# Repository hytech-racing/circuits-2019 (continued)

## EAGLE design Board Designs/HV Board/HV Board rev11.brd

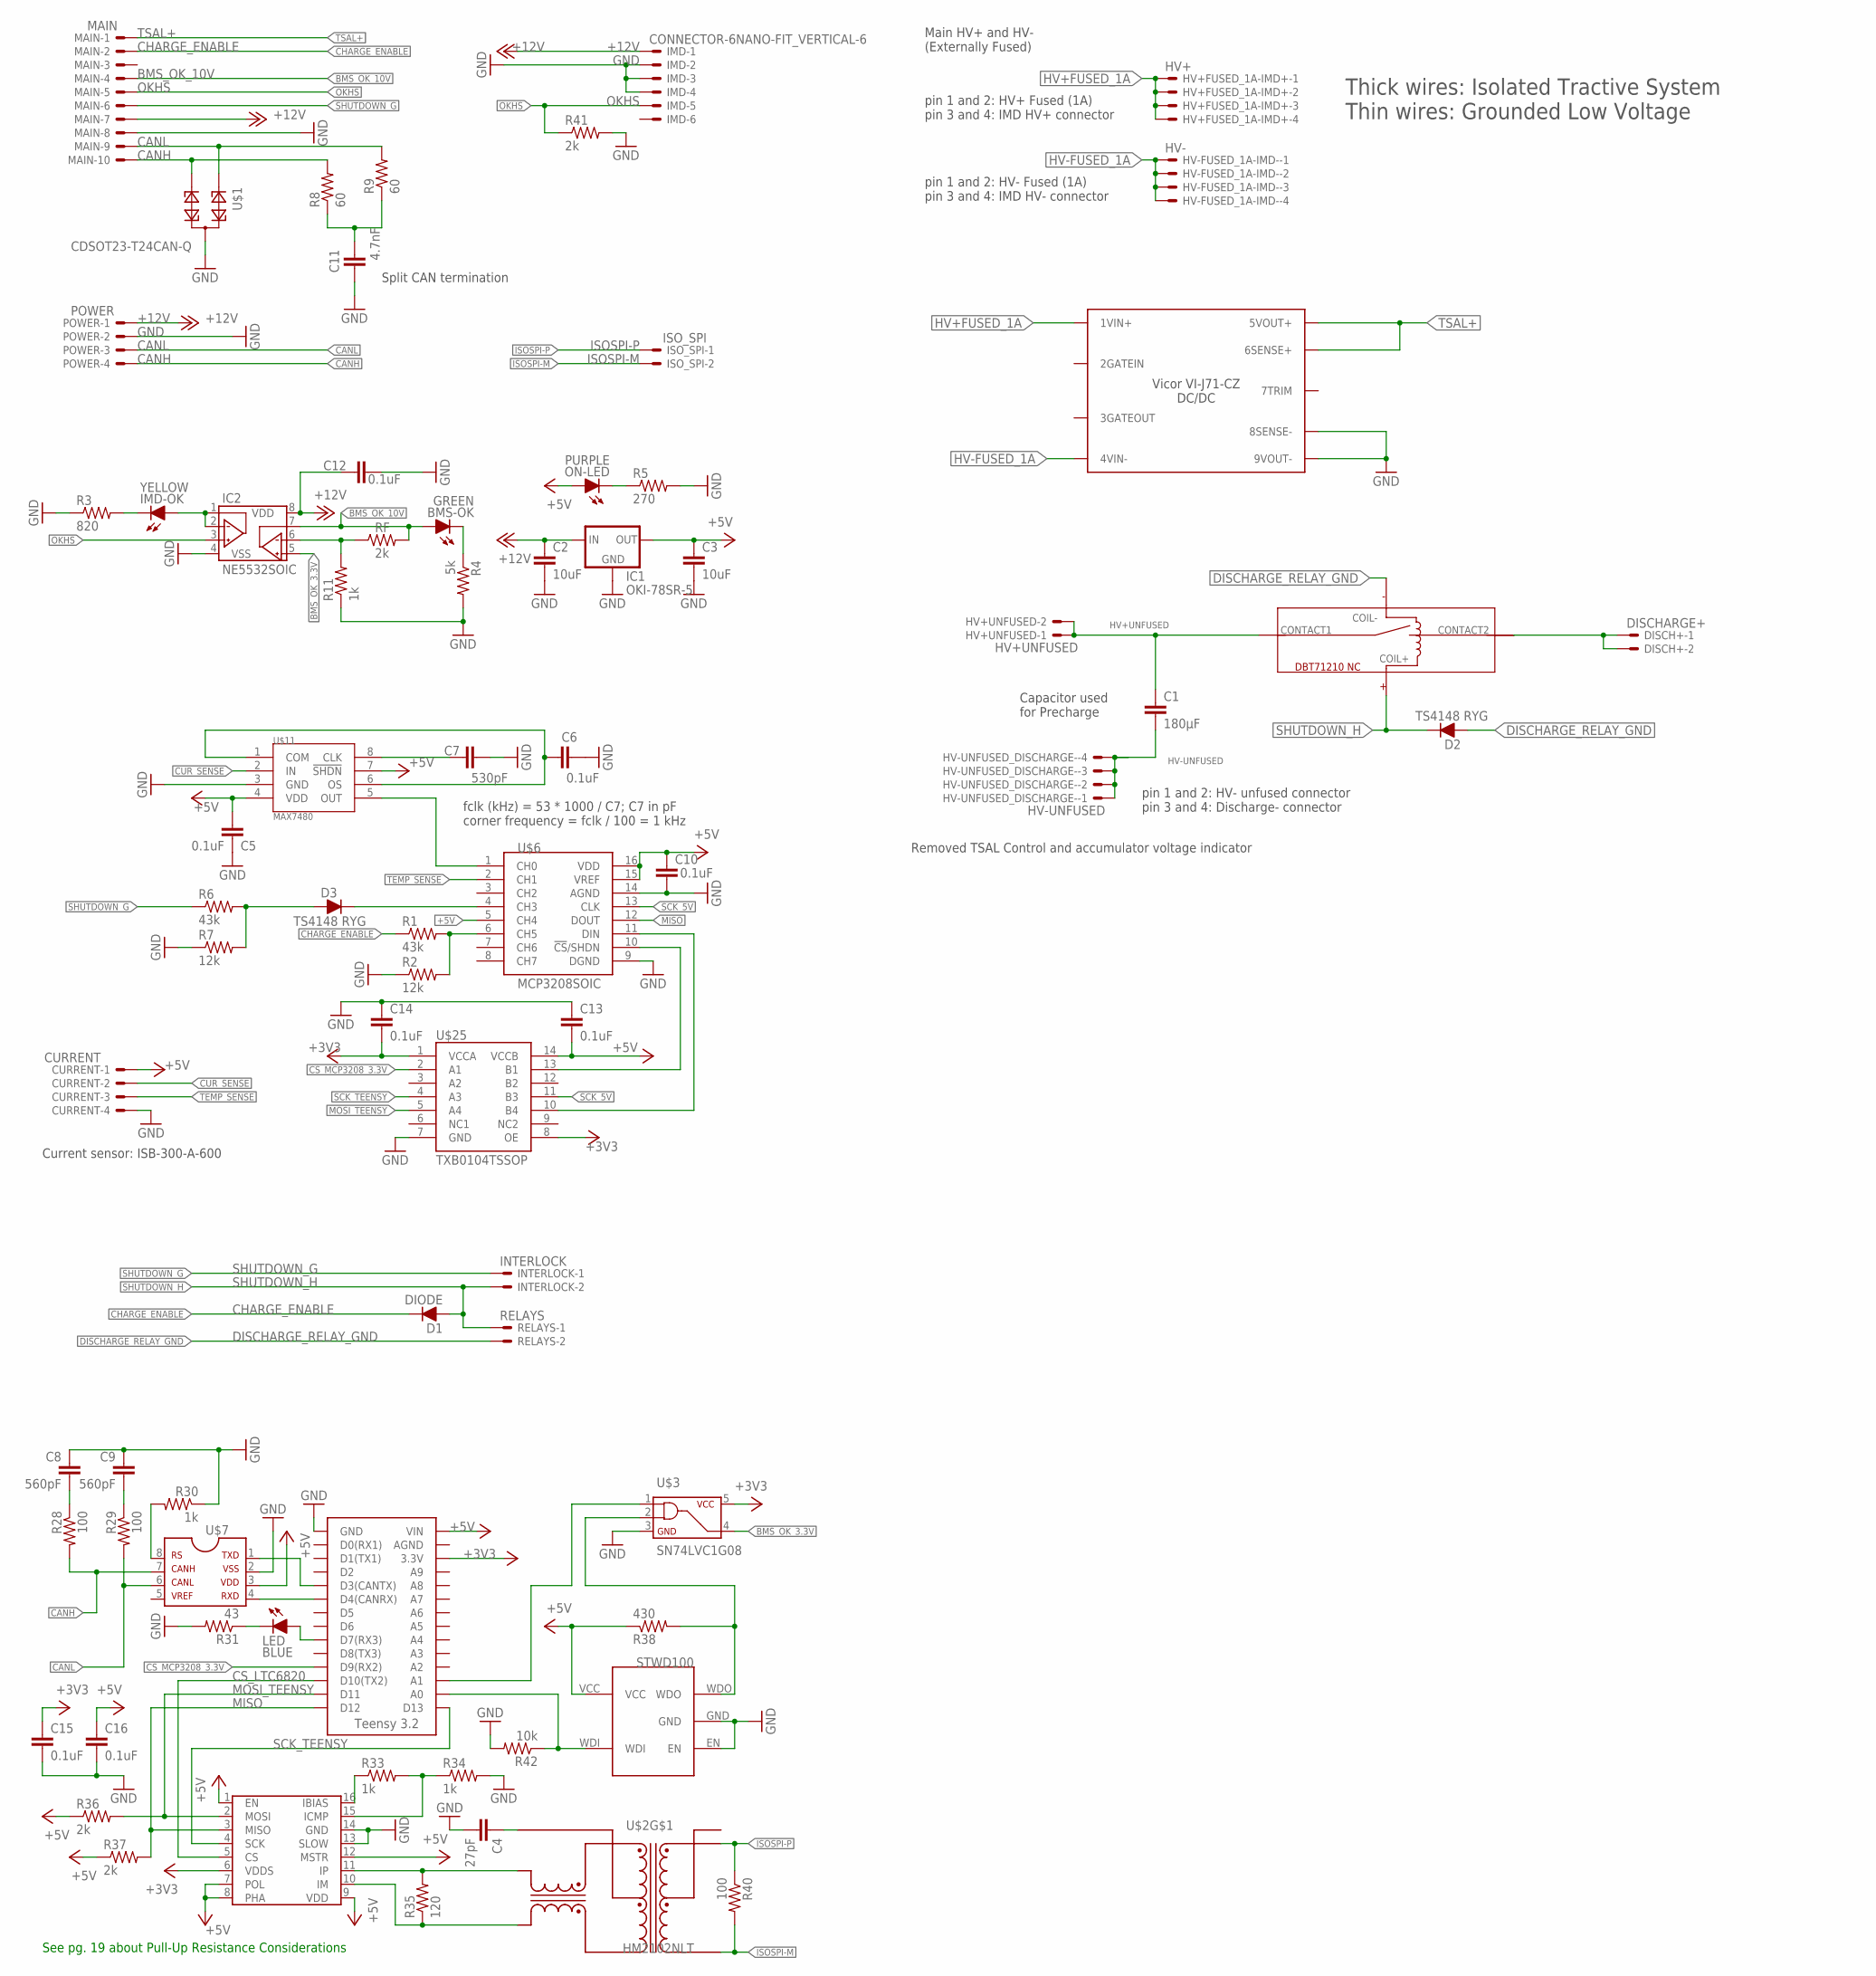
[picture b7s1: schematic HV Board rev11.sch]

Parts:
BMS-OK: GREEN; LED-805
C1: 180µF; LLS2V221MELZ
C2, C3: 10uF; 0805
C4: 27pF; 0805
C5, C6, C10, C12, C13, C14, C15, C16: 0.1uF; 0805
C7: 530pF; 0805
C8, C9: 560pF; 0805
C11: 4.7nF; 0805
CURRENT: CURRENT; NANO-FIT_VERTICAL-4
D1: DIODE; DO-41
D2, D3: TS4148 RYG; 0805_D
DISCH+: DISCHARGE+; NANO-FIT_VERTICAL-2
HV+FUSED_1A-IMD+: HV+; NANO-FIT_VERTICAL-4
HV+UNFUSED: HV+UNFUSED; NANO-FIT_VERTICAL-2
HV-FUSED_1A-IMD-: HV-; NANO-FIT_VERTICAL-4
HV-UNFUSED_DISCHARGE-: HV-UNFUSED; NANO-FIT_VERTICAL-4
IC1: OKI-78SR-5; OKI-78SR
IC2: NE5532SOIC; SOIC-08
IMD: CONNECTOR-6NANO-FIT_VERTICAL-6; NANO-FIT_VERTICAL-6
IMD-OK: YELLOW; LED-805
INTERLOCK: INTERLOCK; NANO-FIT_VERTICAL-2
ISO_SPI: ISO_SPI; NANO-FIT_VERTICAL-2
LED: BLUE; LED-805
MAIN: MAIN; NANO-FIT_VERTICAL-10
ON-LED: PURPLE; LED-805
POWER: POWER; NANO-FIT_VERTICAL-4
R1, R6: 43k; 0805
R2, R7: 12k; 0805
R3: 820; 0805
R4: 5k; 0805
R5: 270; 0805
R8, R9: 60; 0805
R11, R30, R33, R34: 1k; 0805
R28, R29, R40: 100; 0805
R31: 43; 0805
R35: 120; 0805
R36, R37, R41: 2k; 0805
R38: 430; 0805
R42: 10k; 0805
RELAYS: RELAYS; NANO-FIT_VERTICAL-2
RF: 2k; 0805
U$1: CDSOT23-T24CAN-Q; SOT23
U$2: HM2102NLT
U$3: SN74LVC1G08; SOT-23-5
U$4: DBT71210
U$5: HV_DCDC_VI-J71-CZ
U$6: MCP3208SOIC; SOIC-16
U$7: MCP2551; SOIC-08
U$8: LTC6820; MSOP-16
U$9: TEENSY_3.2_SIMPLE
U$10: STWD100; SOT23-5
U$11: MAX7480; SOIC-08
U$25: TXB0104TSSOP; TSSOP-14

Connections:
+3V3: C14.1, C15.2, U$3.5, U$8.6 (VDDS), U$9.3.3V, U$25.1 (VCCA), U$25.8 (OE)
+5V: C3.1, C5.1, C10.1, C13.1, C16.2, CURRENT.P$1, IC1.3 (OUT), ON-LED.A, R36.1, R37.1, R38.1, U$6.5 (CH4), U$6.15 (VREF), U$6.16 (VDD), U$7.3, U$8.1 (EN), U$8.7 (POL), U$8.8 (PHA), U$8.9 (VDD), U$8.12 (MSTR), U$9.VIN, U$10.VCC, U$11.4 (VDD), U$25.14 (VCCB)
+12V: C2.1, C12.1, IC1.1 (IN), IC2.8 (VDD), IMD.P$1, MAIN.P$7, POWER.P$1
BMS_OK_3.3V: IC2.5 (VINB+), U$3.4
BMS_OK_10V: BMS-OK.A, IC2.7 (VOUTB), MAIN.P$4, RF.2
CANH: MAIN.P$10, POWER.P$4, R8.2, R28.2, U$1.2, U$7.7
CANL: MAIN.P$9, POWER.P$3, R9.2, R29.2, U$1.1, U$7.6
CHARGE_ENABLE: D1.C, MAIN.P$2, R1.1
CS_LTC6820: U$8.5 (CS), U$9.D10(TX2)
CS_MCP3208_3.3V: U$9.D9(RX2), U$25.2 (A1)
CUR_SENSE: CURRENT.P$2, U$11.2 (IN)
DISCHARGE_RELAY_GND: D2.A, RELAYS.P$2, U$4.COIL-
GND: C2.2, C3.2, C4.2, C5.2, C6.2, C7.2, C8.1, C9.1, C10.2, C11.1, C12.2, C13.2, C14.2, C15.1, C16.1, CURRENT.P$4, IC1.2 (GND), IC2.4 (VSS), IMD.P$2, IMD.P$3, IMD.P$4, MAIN.P$8, POWER.P$2, R2.1, R3.1, R4.2, R5.2, R7.1, R11.1, R30.1, R31.2, R34.2, R41.2, R42.2, U$1.3, U$3.3, U$5.8SENSE-, U$5.9VOUT-, U$6.9 (DGND), U$6.14 (AGND), U$7.2, U$8.13 (SLOW), U$8.14 (GND), U$9.GND, U$10.EN, U$10.GND, U$11.3 (GND), U$25.7 (GND)
HV+FUSED_1A: HV+FUSED_1A-IMD+.P$1, HV+FUSED_1A-IMD+.P$2, HV+FUSED_1A-IMD+.P$3, HV+FUSED_1A-IMD+.P$4, U$5.1VIN+
HV+UNFUSED: C1.P$1 (1), HV+UNFUSED.P$1, HV+UNFUSED.P$2, U$4.CONTACT1
HV+UNFUSED_FSAE_DISCHARGE: DISCH+.P$1, DISCH+.P$2, U$4.CONTACT2
HV-FUSED_1A: HV-FUSED_1A-IMD-.P$1, HV-FUSED_1A-IMD-.P$2, HV-FUSED_1A-IMD-.P$3, HV-FUSED_1A-IMD-.P$4, U$5.4VIN-
HV-UNFUSED: C1.P$2 (2), HV-UNFUSED_DISCHARGE-.P$1, HV-UNFUSED_DISCHARGE-.P$2, HV-UNFUSED_DISCHARGE-.P$3, HV-UNFUSED_DISCHARGE-.P$4
IM: R35.1, U$2.P$10 (TD-), U$8.10 (IM)
IP: R35.2, U$2.P$12 (TD+), U$8.11 (IP)
ISOSPI-M: ISO_SPI.P$2, R40.2, U$2.P$3 (MX-)
ISOSPI-P: ISO_SPI.P$1, R40.1, U$2.P$1 (MX+)
MISO: R37.2, U$6.12 (DOUT), U$8.3 (MISO), U$9.D12
MOSI_5V: U$6.11 (DIN), U$25.10 (B4)
MOSI_TEENSY: R36.2, U$8.2 (MOSI), U$9.D11, U$25.5 (A4)
unnamed: U$6.1 (CH0), U$11.5 (OUT)
unnamed: C6.1, U$11.1 (COM), U$11.6 (OS)
unnamed: ON-LED.C, R5.1
unnamed: C7.1, U$11.8 (CLK)
unnamed: U$6.10 (!CS!/SHDN), U$25.13 (B1)
unnamed: D3.A, R6.2, R7.2
unnamed: D3.C, U$6.4 (CH3)
unnamed: C11.2, R8.1, R9.1
unnamed: IC2.6 (VINB-), R11.2, RF.1
unnamed: R1.2, R2.2, U$6.6 (CH5)
unnamed: U$7.1, U$9.D3(CANTX)
unnamed: R30.2, U$7.8
unnamed: C8.2, R28.1
unnamed: C9.2, R29.1
unnamed: LED.C, R31.1
unnamed: R33.1, U$8.16 (IBIAS)
unnamed: R33.2, R34.1, U$8.15 (ICMP)
unnamed: C4.1, U$2.P$11 (TCT)
unnamed: U$7.4, U$9.D4(CANRX)
unnamed: LED.A, U$9.D7(RX3)
unnamed: R38.2, U$3.2, U$10.WDO
unnamed: U$3.1, U$9.A1
unnamed: IC2.1 (VOUTA), IC2.2 (VINA-), IMD-OK.A
unnamed: BMS-OK.C, R4.1
unnamed: IMD-OK.C, R3.2
unnamed: R42.1, U$9.A0, U$10.WDI
OKHS: IC2.3 (VINA+), IMD.P$5, MAIN.P$5, R41.1
SCK_5V: U$6.13 (CLK), U$25.11 (B3)
SCK_TEENSY: U$8.4 (SCK), U$9.D13, U$25.4 (A3)
SHUTDOWN_G: INTERLOCK.P$1, MAIN.P$6, R6.1
SHUTDOWN_H: D1.A, D2.C, INTERLOCK.P$2, RELAYS.P$1, U$4.COIL+
TEMP_SENSE: CURRENT.P$3, U$6.2 (CH1)
TSAL+: MAIN.P$1, U$5.5VOUT+, U$5.6SENSE+

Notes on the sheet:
Current sensor: ISB-300-A-600
Main HV+ and HV- (Externally Fused)
Thick wires: Isolated Tractive System Thin wires: Grounded Low Voltage
See pg. 19 about Pull-Up Resistance Considerations
Capacitor used for Precharge
Removed TSAL Control and accumulator voltage indicator
pin 1 and 2: HV+ Fused (1A) pin 3 and 4: IMD HV+ connector
pin 1 and 2: HV- Fused (1A) pin 3 and 4: IMD HV- connector
pin 1 and 2: HV- unfused connector pin 3 and 4: Discharge- connector
fclk (kHz) = 53 * 1000 / C7; C7 in pF corner frequency = fclk / 100 = 1 kHz
Split CAN termination

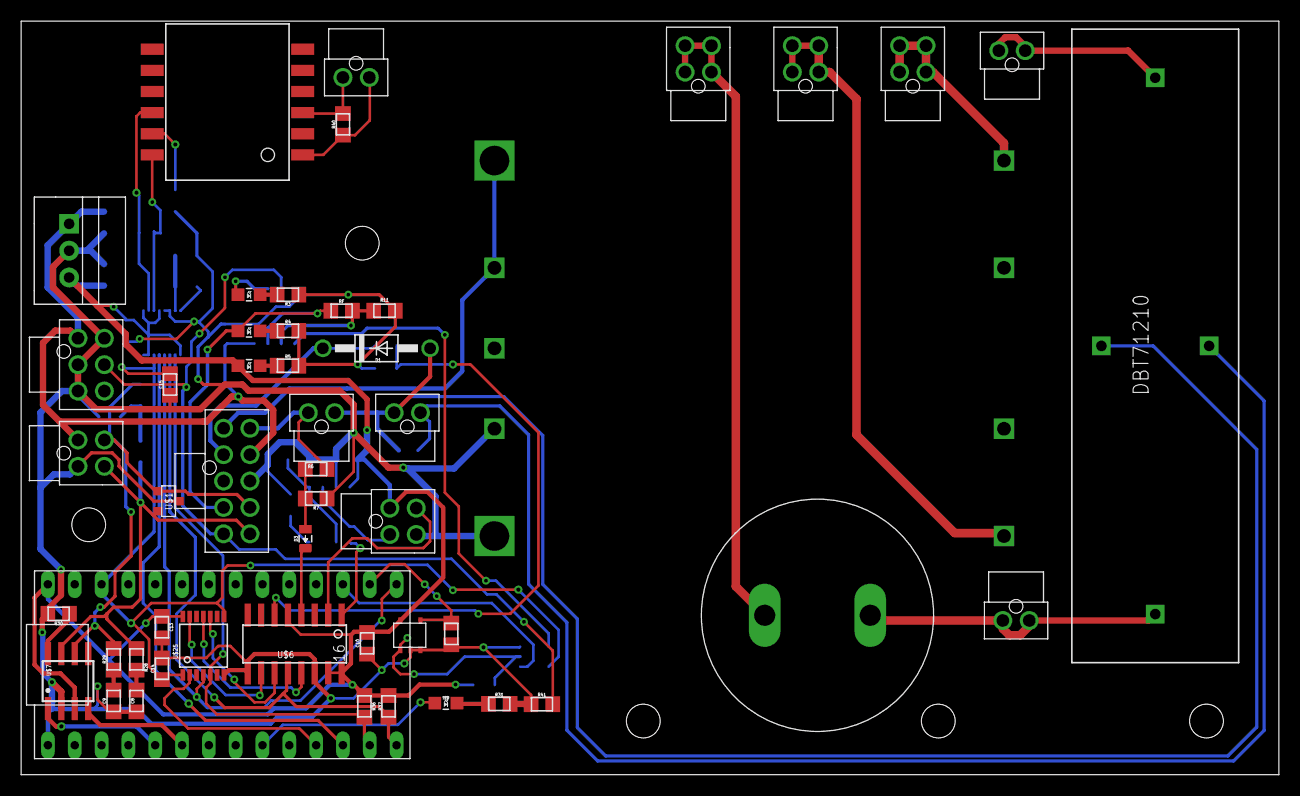
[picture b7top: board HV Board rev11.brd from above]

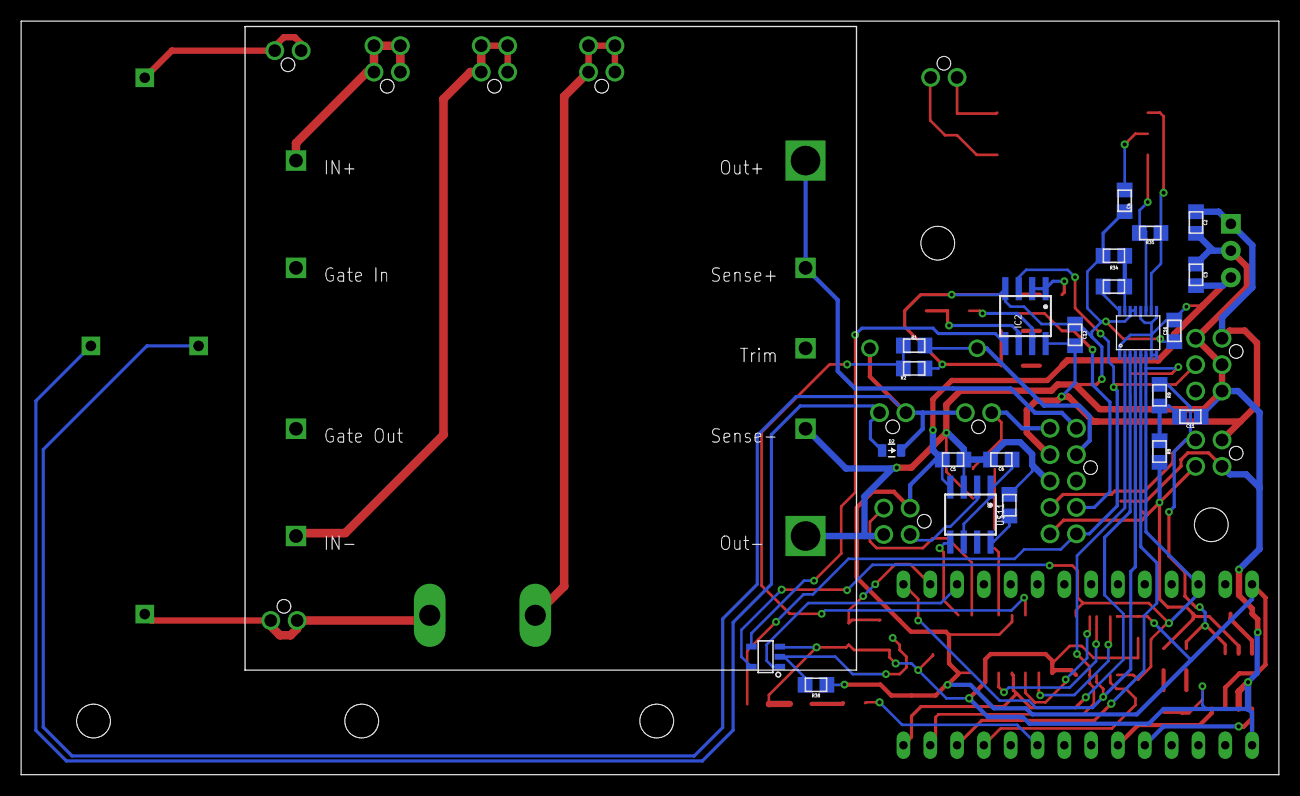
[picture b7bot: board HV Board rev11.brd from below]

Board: 2 copper layers, 119.1 x 71.4 mm, 73 parts (23 on the bottom side), 58 nets.

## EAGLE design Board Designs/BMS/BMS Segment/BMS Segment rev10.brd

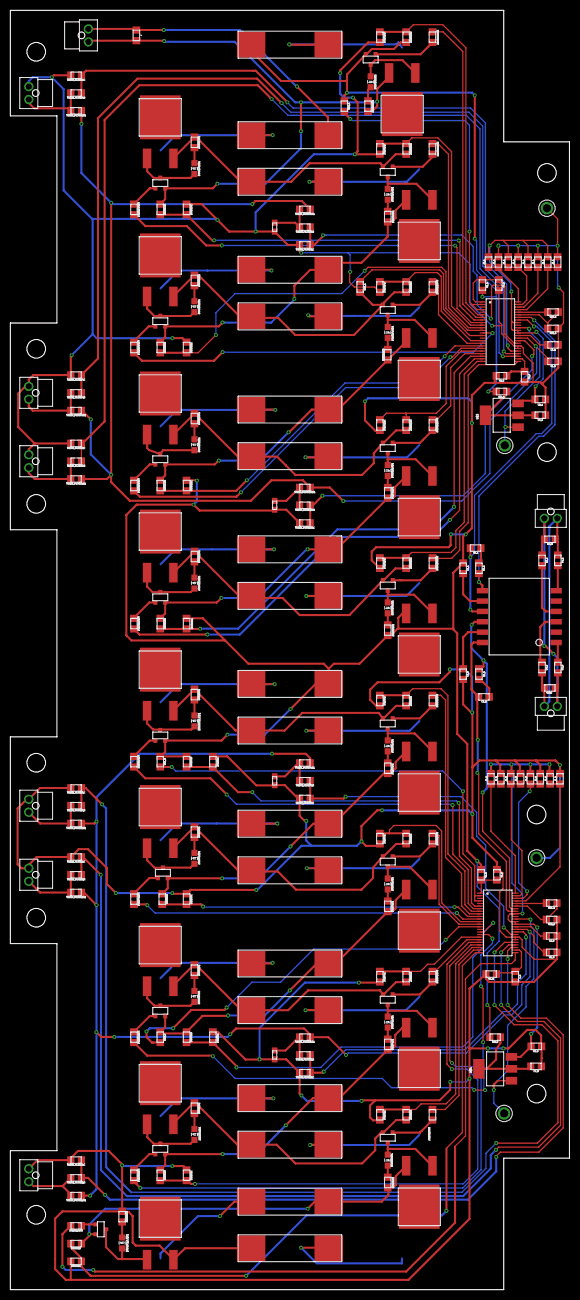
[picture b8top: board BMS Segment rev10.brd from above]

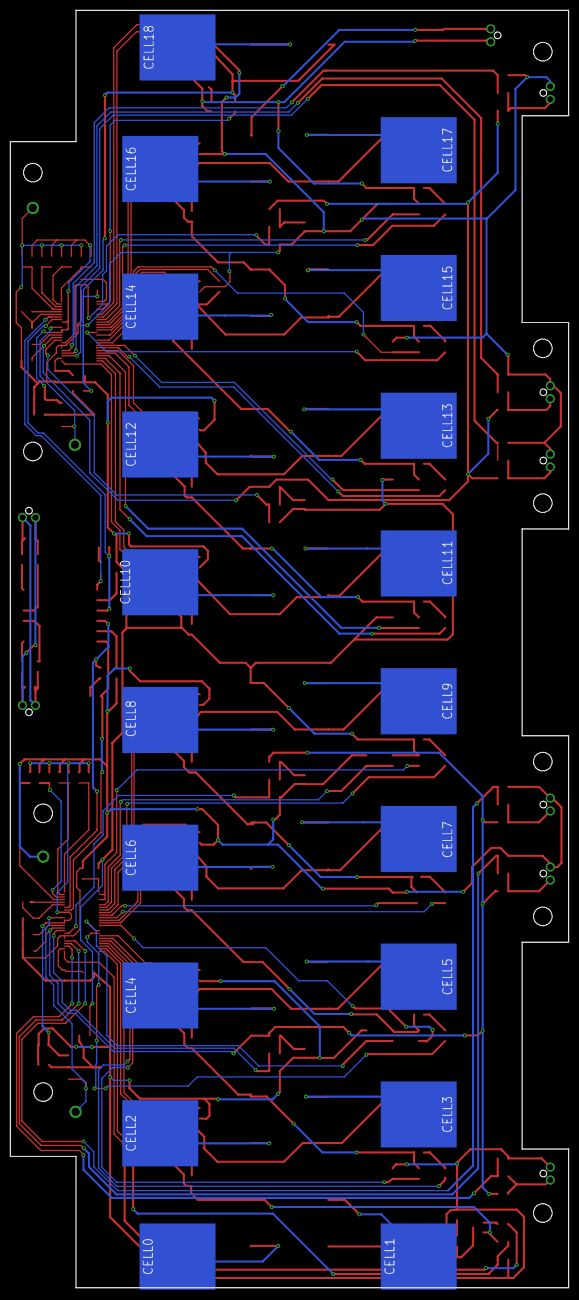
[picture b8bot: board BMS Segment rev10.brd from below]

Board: 2 copper layers, 108.0 x 247.1 mm, 271 parts (19 on the bottom side), 193 nets.

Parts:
AMS_TEST_PORT1: CONNECTOR-2NANO-FIT_VERTICAL-2; NANO-FIT_VERTICAL-2
C1_A, C1_B, C2_A, C2_B, C8_A, C8_B: 1uF; 0805
C3_A, C3_B: 15pF; 0805
C4_A, C4_B, C5_A: 10nF; 0805
C6_A, C6_B, C7_A, C7_B: 100nF; 0805
CELL0, CELL1, CELL2, CELL3, CELL4, CELL5, CELL6, CELL7, CELL8, CELL9, CELL10, CELL11, CELL12, CELL13, CELL14, CELL15, CELL16, CELL17, CELL18: BATTERY_SPRING_KEYSTONE5222; KEYSTONE5222
C_5: 10nF; 0805
DRAIN1:C, DRAIN2:C, DRAIN3:C, DRAIN4:C, DRAIN5:C, DRAIN6:C, DRAIN7:C, DRAIN8:C, DRAIN9:C, DRAIN10:C, DRAIN11:C, DRAIN12:C, DRAIN13:C, DRAIN14:C, DRAIN15:C, DRAIN16:C, DRAIN17:C, DRAIN18:C: 10nF; 0805
DRAIN1:DISCHARGE, DRAIN2:DISCHARGE, DRAIN3:DISCHARGE, DRAIN4:DISCHARGE, DRAIN5:DISCHARGE, DRAIN6:DISCHARGE, DRAIN7:DISCHARGE, DRAIN8:DISCHARGE, DRAIN9:DISCHARGE, DRAIN10:DISCHARGE, DRAIN11:DISCHARGE, DRAIN12:DISCHARGE, DRAIN13:DISCHARGE, DRAIN14:DISCHARGE, DRAIN15:DISCHARGE, DRAIN16:DISCHARGE, DRAIN17:DISCHARGE, DRAIN18:DISCHARGE: 5R; PWR163
DRAIN1:GATE, DRAIN2:GATE, DRAIN3:GATE, DRAIN4:GATE, DRAIN5:GATE, DRAIN6:GATE, DRAIN7:GATE, DRAIN8:GATE, DRAIN9:GATE, DRAIN10:GATE, DRAIN11:GATE, DRAIN12:GATE, DRAIN13:GATE, DRAIN14:GATE, DRAIN15:GATE, DRAIN16:GATE, DRAIN17:GATE, DRAIN18:GATE: 3K3; 0805
DRAIN1:LED1, DRAIN2:LED1, DRAIN3:LED1, DRAIN4:LED1, DRAIN5:LED1, DRAIN6:LED1, DRAIN7:LED1, DRAIN8:LED1, DRAIN9:LED1, DRAIN10:LED1, DRAIN11:LED1, DRAIN12:LED1, DRAIN13:LED1, DRAIN14:LED1, DRAIN15:LED1, DRAIN16:LED1, DRAIN17:LED1, DRAIN18:LED1: RED; LED-805
DRAIN1:PFET, DRAIN2:PFET, DRAIN3:PFET, DRAIN4:PFET, DRAIN5:PFET, DRAIN6:PFET, DRAIN7:PFET, DRAIN8:PFET, DRAIN9:PFET, DRAIN10:PFET, DRAIN11:PFET, DRAIN12:PFET, DRAIN13:PFET, DRAIN14:PFET, DRAIN15:PFET, DRAIN16:PFET, DRAIN17:PFET, DRAIN18:PFET: P-CHANNEL_MOSFET_DMP3099L-7; SOT23
DRAIN1:R, DRAIN2:R, DRAIN3:R, DRAIN4:R, DRAIN5:R, DRAIN6:R, DRAIN7:R, DRAIN8:R, DRAIN9:R, DRAIN10:R, DRAIN11:R, DRAIN12:R, DRAIN13:R, DRAIN14:R, DRAIN15:R, DRAIN16:R, DRAIN17:R, DRAIN18:R: 100R; 0805
DRAIN1:R1, DRAIN2:R1, DRAIN3:R1, DRAIN4:R1, DRAIN5:R1, DRAIN6:R1, DRAIN7:R1, DRAIN8:R1, DRAIN9:R1, DRAIN10:R1, DRAIN11:R1, DRAIN12:R1, DRAIN13:R1, DRAIN14:R1, DRAIN15:R1, DRAIN16:R1, DRAIN17:R1, DRAIN18:R1: 150R; 0805
F0, F1, F2, F3, F4, F5, F6, F7, F8, F9, F10, F11, F12, F13, F14, F15, F16, F17, F18: 0001.2704.11; 5X20MM_FUSE
ISOSPI_A: CONNECTOR-2NANO-FIT_VERTICAL-2; NANO-FIT_VERTICAL-2
ISOSPI_B: CONNECTOR-2NANO-FIT_VERTICAL-2; NANO-FIT_VERTICAL-2
J: 0R; 0805
J1_A, J1_B, J2_A, J2_B, J3_A, J3_B, J4_A, J4_B, J5_A, J5_B, J6_A, J6_B, J7_A, J7_B, J8_A, J8_B: 0805
R1_A, R1_B, R2_A, R2_B: 100R; 0805
R3_A, R3_B: 402R; 0805
R4_A, R4_B, R5_A, R5_B: 22R; 0805
RB1_A, RB1_B: 1K2; 0805
RB2_A, RB2_B: 806R; 0805
RIN_A: 100R; 0805
RIN_B: 100R; 0805
RM_A: 100R; 0805
RM_B: 100R; 0805
RU1_A, RU1_B, RU2_A, RU2_B: 100R; 0805
THERM1, THERM2, THERM3, THERM4: 10K; 0603
THERM1_A, THERM1_B, THERM2_A, THERM2_B, THERM3_A, THERM3_B: Th1; NANO-FIT_VERTICAL-2
THERM_FILTER1:C, THERM_FILTER2:C, THERM_FILTER3:C, THERM_FILTER4:C, THERM_FILTER5:C, THERM_FILTER6:C, THERM_FILTER7:C, THERM_FILTER8:C, THERM_FILTER9:C, THERM_FILTER10:C: 10nF; 0805
THERM_FILTER1:R, THERM_FILTER2:R, THERM_FILTER3:R, THERM_FILTER4:R, THERM_FILTER5:R, THERM_FILTER6:R, THERM_FILTER7:R, THERM_FILTER8:R, THERM_FILTER9:R, THERM_FILTER10:R: 100R; 0805
THERM_FILTER1:R1, THERM_FILTER2:R1, THERM_FILTER3:R1, THERM_FILTER4:R1, THERM_FILTER5:R1, THERM_FILTER6:R1, THERM_FILTER7:R1, THERM_FILTER8:R1, THERM_FILTER9:R1, THERM_FILTER10:R1: 10K; 0805
TRANSFORMER: HM2102NLT
U$1, U$2: LTC6804-2; LTC6804
U$3, U$4: SOT223
U$5, U$6, U$7, U$8: TEST_POINT

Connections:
C0_A: C5_A.1, R2_A.2, U$1.26
C0_B: C_5.1, R2_B.2, U$2.26
C1_A: DRAIN10:C.1, DRAIN10:R.2, U$1.24
C1_B: DRAIN1:C.1, DRAIN1:R.2, U$2.24
C2_A: DRAIN11:C.1, DRAIN11:R.2, U$1.22
C2_B: DRAIN2:C.1, DRAIN2:R.2, U$2.22
C3_A: DRAIN12:C.1, DRAIN12:R.2, U$1.20
C3_B: DRAIN3:C.1, DRAIN3:R.2, U$2.20
C4_A: DRAIN13:C.1, DRAIN13:R.2, U$1.18
C4_B: DRAIN4:C.1, DRAIN4:R.2, U$2.18
C5_A: DRAIN14:C.1, DRAIN14:R.2, U$1.16
C5_B: DRAIN5:C.1, DRAIN5:R.2, U$2.16
C7_A: DRAIN15:C.1, DRAIN15:R.2, U$1.12
C7_B: DRAIN6:C.1, DRAIN6:R.2, U$2.12
C8_A: DRAIN16:C.1, DRAIN16:R.2, U$1.10
C8_B: DRAIN7:C.1, DRAIN7:R.2, U$2.10
C9_A: DRAIN17:C.1, DRAIN17:R.2, U$1.8
C9_B: DRAIN8:C.1, DRAIN8:R.2, U$2.8
C10_A: DRAIN18:C.1, DRAIN18:R.2, U$1.6
C10_B: DRAIN9:C.1, DRAIN9:R.2, U$2.6
CC0: CELL0.P$1, F0.P$1
CC1: CELL1.P$1, F1.P$1
CC2: CELL2.P$1, F2.P$1
CC3: CELL3.P$1, F3.P$1
CC4: CELL4.P$1, F4.P$1
CC5: CELL5.P$1, F5.P$1
CC6: CELL6.P$1, F6.P$1
CC7: CELL7.P$1, F7.P$1
CC8: CELL8.P$1, F8.P$1
CC9: CELL9.P$1, F9.P$1
CC10: CELL10.P$1, F10.P$1
CC11: CELL11.P$1, F11.P$1
CC12: CELL12.P$1, F12.P$1
CC13: CELL13.P$1, F13.P$1
CC14: CELL14.P$1, F14.P$1
CC15: CELL15.P$1, F15.P$1
CC16: CELL16.P$1, F16.P$1
CC17: CELL17.P$1, F17.P$1
CC18: CELL18.P$1, F18.P$1
DRAIN1:GATE: DRAIN1:GATE.1, DRAIN1:PFET.1
DRAIN1:N$1: DRAIN1:DISCHARGE.1, DRAIN1:LED1.A, DRAIN1:PFET.3
DRAIN1:N$2: DRAIN1:LED1.C, DRAIN1:R1.2
DRAIN2:GATE: DRAIN2:GATE.1, DRAIN2:PFET.1
DRAIN2:N$1: DRAIN2:DISCHARGE.1, DRAIN2:LED1.A, DRAIN2:PFET.3
DRAIN2:N$2: DRAIN2:LED1.C, DRAIN2:R1.2
DRAIN3:GATE: DRAIN3:GATE.1, DRAIN3:PFET.1
DRAIN3:N$1: DRAIN3:DISCHARGE.1, DRAIN3:LED1.A, DRAIN3:PFET.3
DRAIN3:N$2: DRAIN3:LED1.C, DRAIN3:R1.2
DRAIN4:GATE: DRAIN4:GATE.1, DRAIN4:PFET.1
DRAIN4:N$1: DRAIN4:DISCHARGE.1, DRAIN4:LED1.A, DRAIN4:PFET.3
DRAIN4:N$2: DRAIN4:LED1.C, DRAIN4:R1.2
DRAIN5:GATE: DRAIN5:GATE.1, DRAIN5:PFET.1
DRAIN5:N$1: DRAIN5:DISCHARGE.1, DRAIN5:LED1.A, DRAIN5:PFET.3
DRAIN5:N$2: DRAIN5:LED1.C, DRAIN5:R1.2
DRAIN6:GATE: DRAIN6:GATE.1, DRAIN6:PFET.1
DRAIN6:N$1: DRAIN6:DISCHARGE.1, DRAIN6:LED1.A, DRAIN6:PFET.3
DRAIN6:N$2: DRAIN6:LED1.C, DRAIN6:R1.2
DRAIN7:GATE: DRAIN7:GATE.1, DRAIN7:PFET.1
DRAIN7:N$1: DRAIN7:DISCHARGE.1, DRAIN7:LED1.A, DRAIN7:PFET.3
DRAIN7:N$2: DRAIN7:LED1.C, DRAIN7:R1.2
DRAIN8:GATE: DRAIN8:GATE.1, DRAIN8:PFET.1
DRAIN8:N$1: DRAIN8:DISCHARGE.1, DRAIN8:LED1.A, DRAIN8:PFET.3
DRAIN8:N$2: DRAIN8:LED1.C, DRAIN8:R1.2
DRAIN9:GATE: DRAIN9:GATE.1, DRAIN9:PFET.1
DRAIN9:N$1: DRAIN9:DISCHARGE.1, DRAIN9:LED1.A, DRAIN9:PFET.3
DRAIN9:N$2: DRAIN9:LED1.C, DRAIN9:R1.2
DRAIN10:GATE: DRAIN10:GATE.1, DRAIN10:PFET.1
DRAIN10:N$1: DRAIN10:DISCHARGE.1, DRAIN10:LED1.A, DRAIN10:PFET.3
DRAIN10:N$2: DRAIN10:LED1.C, DRAIN10:R1.2
DRAIN11:GATE: DRAIN11:GATE.1, DRAIN11:PFET.1
DRAIN11:N$1: DRAIN11:DISCHARGE.1, DRAIN11:LED1.A, DRAIN11:PFET.3
DRAIN11:N$2: DRAIN11:LED1.C, DRAIN11:R1.2
DRAIN12:GATE: DRAIN12:GATE.1, DRAIN12:PFET.1
DRAIN12:N$1: DRAIN12:DISCHARGE.1, DRAIN12:LED1.A, DRAIN12:PFET.3
DRAIN12:N$2: DRAIN12:LED1.C, DRAIN12:R1.2
DRAIN13:GATE: DRAIN13:GATE.1, DRAIN13:PFET.1
DRAIN13:N$1: DRAIN13:DISCHARGE.1, DRAIN13:LED1.A, DRAIN13:PFET.3
DRAIN13:N$2: DRAIN13:LED1.C, DRAIN13:R1.2
DRAIN14:GATE: DRAIN14:GATE.1, DRAIN14:PFET.1
DRAIN14:N$1: DRAIN14:DISCHARGE.1, DRAIN14:LED1.A, DRAIN14:PFET.3
DRAIN14:N$2: DRAIN14:LED1.C, DRAIN14:R1.2
DRAIN15:GATE: DRAIN15:GATE.1, DRAIN15:PFET.1
DRAIN15:N$1: DRAIN15:DISCHARGE.1, DRAIN15:LED1.A, DRAIN15:PFET.3
DRAIN15:N$2: DRAIN15:LED1.C, DRAIN15:R1.2
DRAIN16:GATE: DRAIN16:GATE.1, DRAIN16:PFET.1
DRAIN16:N$1: DRAIN16:DISCHARGE.1, DRAIN16:LED1.A, DRAIN16:PFET.3
DRAIN16:N$2: DRAIN16:LED1.C, DRAIN16:R1.2
DRAIN17:GATE: DRAIN17:GATE.1, DRAIN17:PFET.1
DRAIN17:N$1: DRAIN17:DISCHARGE.1, DRAIN17:LED1.A, DRAIN17:PFET.3
DRAIN17:N$2: DRAIN17:LED1.C, DRAIN17:R1.2
DRAIN18:GATE: DRAIN18:GATE.1, DRAIN18:PFET.1
DRAIN18:N$1: DRAIN18:DISCHARGE.1, DRAIN18:LED1.A, DRAIN18:PFET.3
DRAIN18:N$2: DRAIN18:LED1.C, DRAIN18:R1.2
DRIVE_A: U$1.38, U$3.1, U$8.P$1
DRIVE_B: U$2.38, U$4.1, U$7.P$1
GPIO1_A: THERM_FILTER6:C.1, THERM_FILTER6:R.1, U$1.27
GPIO1_B: THERM_FILTER1:C.1, THERM_FILTER1:R.1, U$2.27
GPIO2_A: THERM_FILTER7:C.1, THERM_FILTER7:R.1, U$1.28
GPIO2_B: THERM_FILTER2:C.1, THERM_FILTER2:R.1, U$2.28
GPIO3_A: THERM_FILTER8:C.1, THERM_FILTER8:R.1, U$1.29
GPIO3_B: THERM_FILTER3:C.1, THERM_FILTER3:R.1, U$2.29
GPIO4_A: THERM_FILTER9:C.1, THERM_FILTER9:R.1, U$1.32
GPIO4_B: THERM_FILTER4:C.1, THERM_FILTER4:R.1, U$2.32
GPIO5_A: THERM_FILTER10:C.1, THERM_FILTER10:R.1, U$1.33
GPIO5_B: THERM_FILTER5:C.1, THERM_FILTER5:R.1, U$2.33
IM_A: C3_A.2, TRANSFORMER.P$9, U$1.41
IM_B: C3_B.2, TRANSFORMER.P$12, U$2.41
IP_A: R3_A.1, TRANSFORMER.P$7, U$1.42
IP_B: R3_B.1, TRANSFORMER.P$10, U$2.42
ISOSPI-M: ISOSPI_A.P$2, ISOSPI_B.P$2, R5_A.2, R5_B.2, RM_A.2, RM_B.2
ISOSPI-P: ISOSPI_A.P$1, ISOSPI_B.P$1, R4_A.2, R4_B.2, RM_A.1, RM_B.1
unnamed: C4_B.1, TRANSFORMER.P$11
unnamed: RB1_B.2, U$2.44
unnamed: THERM1_B.P$1, THERM_FILTER1:R.2, THERM_FILTER1:R1.2
unnamed: RB1_B.1, RB2_B.2, U$2.43
unnamed: R4_B.1, TRANSFORMER.P$3
unnamed: RB1_A.2, U$1.44
unnamed: R5_B.1, TRANSFORMER.P$1
unnamed: J7_B.1, J8_B.1, U$2.48
unnamed: J5_B.1, J6_B.1, U$2.47
unnamed: C3_B.1, R3_B.2
unnamed: J3_B.1, J4_B.1, U$2.46
unnamed: J1_B.1, J2_B.1, U$2.45
unnamed: THERM1.2, THERM_FILTER5:R.2, THERM_FILTER5:R1.2
unnamed: THERM2_B.P$1, THERM_FILTER2:R.2, THERM_FILTER2:R1.2
unnamed: THERM2.2, THERM_FILTER4:R.2, THERM_FILTER4:R1.2
unnamed: RB1_A.1, RB2_A.2, U$1.43
unnamed: C4_A.1, TRANSFORMER.P$8
unnamed: R4_A.1, TRANSFORMER.P$6
unnamed: R5_A.1, TRANSFORMER.P$4
unnamed: C3_A.1, R3_A.2
unnamed: THERM3_B.P$1, THERM_FILTER3:R.2, THERM_FILTER3:R1.2
unnamed: J7_A.1, J8_A.1, U$1.48
unnamed: J5_A.1, J6_A.1, U$1.47
unnamed: J3_A.1, J4_A.1, U$1.46
unnamed: J1_A.1, J2_A.1, U$1.45
unnamed: THERM4.2, THERM_FILTER9:R.2, THERM_FILTER9:R1.2
unnamed: THERM3_A.P$1, THERM_FILTER8:R.2, THERM_FILTER8:R1.2
unnamed: THERM3.2, THERM_FILTER10:R.2, THERM_FILTER10:R1.2
unnamed: THERM2_A.P$1, THERM_FILTER7:R.2, THERM_FILTER7:R1.2
unnamed: THERM1_A.P$1, THERM_FILTER6:R.2, THERM_FILTER6:R1.2
S1_A: DRAIN10:GATE.2, U$1.25
S1_B: DRAIN1:GATE.2, U$2.25
S2_A: DRAIN11:GATE.2, U$1.23
S2_B: DRAIN2:GATE.2, U$2.23
S3_A: DRAIN12:GATE.2, U$1.21
S3_B: DRAIN3:GATE.2, U$2.21
S4_A: DRAIN13:GATE.2, U$1.19
S4_B: DRAIN4:GATE.2, U$2.19
S5_A: DRAIN14:GATE.2, U$1.17
S5_B: DRAIN5:GATE.2, U$2.17
S7_A: DRAIN15:GATE.2, U$1.13
S7_B: DRAIN6:GATE.2, U$2.13
S8_A: DRAIN16:GATE.2, U$1.11
S8_B: DRAIN7:GATE.2, U$2.11
S9_A: DRAIN17:GATE.2, U$1.9
S9_B: DRAIN8:GATE.2, U$2.9
S10_A: DRAIN18:GATE.2, U$1.7
S10_B: DRAIN9:GATE.2, U$2.7
SENSE1: DRAIN1:PFET.2, DRAIN1:R.1, DRAIN2:DISCHARGE.2, DRAIN2:R1.1, F1.P$2
SENSE2: DRAIN2:PFET.2, DRAIN2:R.1, DRAIN3:DISCHARGE.2, DRAIN3:R1.1, F2.P$2
SENSE3: DRAIN3:PFET.2, DRAIN3:R.1, DRAIN4:DISCHARGE.2, DRAIN4:R1.1, F3.P$2
SENSE4: DRAIN4:PFET.2, DRAIN4:R.1, DRAIN5:DISCHARGE.2, DRAIN5:R1.1, F4.P$2
SENSE5: DRAIN5:PFET.2, DRAIN5:R.1, DRAIN6:DISCHARGE.2, DRAIN6:R1.1, F5.P$2, RU2_B.1
SENSE6: DRAIN6:PFET.2, DRAIN6:R.1, DRAIN7:DISCHARGE.2, DRAIN7:R1.1, F6.P$2
SENSE7: DRAIN7:PFET.2, DRAIN7:R.1, DRAIN8:DISCHARGE.2, DRAIN8:R1.1, F7.P$2
SENSE8: DRAIN8:PFET.2, DRAIN8:R.1, DRAIN9:DISCHARGE.2, DRAIN9:R1.1, F8.P$2
SENSE10: DRAIN10:PFET.2, DRAIN10:R.1, DRAIN11:DISCHARGE.2, DRAIN11:R1.1, F10.P$2
SENSE11: DRAIN11:PFET.2, DRAIN11:R.1, DRAIN12:DISCHARGE.2, DRAIN12:R1.1, F11.P$2
SENSE12: DRAIN12:PFET.2, DRAIN12:R.1, DRAIN13:DISCHARGE.2, DRAIN13:R1.1, F12.P$2
SENSE13: DRAIN13:PFET.2, DRAIN13:R.1, DRAIN14:DISCHARGE.2, DRAIN14:R1.1, F13.P$2
SENSE14: DRAIN14:PFET.2, DRAIN14:R.1, DRAIN15:DISCHARGE.2, DRAIN15:R1.1, F14.P$2, RU2_A.1
SENSE15: DRAIN15:PFET.2, DRAIN15:R.1, DRAIN16:DISCHARGE.2, DRAIN16:R1.1, F15.P$2
SENSE16: DRAIN16:PFET.2, DRAIN16:R.1, DRAIN17:DISCHARGE.2, DRAIN17:R1.1, F16.P$2
SENSE17: AMS_TEST_PORT1.P$2, DRAIN17:PFET.2, DRAIN17:R.1, DRAIN18:DISCHARGE.2, DRAIN18:R1.1, J.2
SENSE17_J: AMS_TEST_PORT1.P$1, F17.P$2, J.1
SENSE18: DRAIN18:PFET.2, DRAIN18:R.1, F18.P$2, R1_A.1, RIN_A.1, RU1_A.1
UNUSED1_A: RU1_A.2, U$1.2, U$1.4
UNUSED1_B: RU1_B.2, U$2.2, U$2.4
UNUSED2_A: RU2_A.2, U$1.14
UNUSED2_B: RU2_B.2, U$2.14
V+_A: C6_A.1, R1_A.2, U$1.1
V+_B: C6_B.1, R1_B.2, U$2.1
V-_A: C1_A.2, C2_A.2, C4_A.2, C5_A.2, C6_A.2, C7_A.2, C8_A.2, DRAIN9:PFET.2, DRAIN9:R.1, DRAIN10:C.2, DRAIN10:DISCHARGE.2, DRAIN10:R1.1, DRAIN11:C.2, DRAIN12:C.2, DRAIN13:C.2, DRAIN14:C.2, DRAIN15:C.2, DRAIN16:C.2, DRAIN17:C.2, DRAIN18:C.2, F9.P$2, J1_A.2, J3_A.2, J5_A.2, J7_A.2, R1_B.1, R2_A.1, RB2_A.1, RIN_B.1, RU1_B.1, THERM1_A.P$2, THERM2_A.P$2, THERM3.1, THERM3_A.P$2, THERM4.1, THERM_FILTER6:C.2, THERM_FILTER7:C.2, THERM_FILTER8:C.2, THERM_FILTER9:C.2, THERM_FILTER10:C.2, U$1.30, U$1.31, U$5.P$1
V-_B: C1_B.2, C2_B.2, C4_B.2, C6_B.2, C7_B.2, C8_B.2, C_5.2, DRAIN1:C.2, DRAIN1:DISCHARGE.2, DRAIN1:R1.1, DRAIN2:C.2, DRAIN3:C.2, DRAIN4:C.2, DRAIN5:C.2, DRAIN6:C.2, DRAIN7:C.2, DRAIN8:C.2, DRAIN9:C.2, F0.P$2, J1_B.2, J3_B.2, J5_B.2, J7_B.2, R2_B.1, RB2_B.1, THERM1.1, THERM1_B.P$2, THERM2.1, THERM2_B.P$2, THERM3_B.P$2, THERM_FILTER1:C.2, THERM_FILTER2:C.2, THERM_FILTER3:C.2, THERM_FILTER4:C.2, THERM_FILTER5:C.2, U$2.30, U$2.31, U$6.P$1
VIN_A: C7_A.1, RIN_A.2, U$3.2, U$3.4
VIN_B: C7_B.1, RIN_B.2, U$4.2, U$4.4
VREF1_A: C2_A.1, U$1.35
VREF1_B: C2_B.1, U$2.35
VREF2_A: C1_A.1, THERM_FILTER6:R1.1, THERM_FILTER7:R1.1, THERM_FILTER8:R1.1, THERM_FILTER9:R1.1, THERM_FILTER10:R1.1, U$1.34
VREF2_B: C1_B.1, THERM_FILTER1:R1.1, THERM_FILTER2:R1.1, THERM_FILTER3:R1.1, THERM_FILTER4:R1.1, THERM_FILTER5:R1.1, U$2.34
VREG_A: C8_A.1, J2_A.2, J4_A.2, J6_A.2, J8_A.2, U$1.36, U$1.37, U$1.40, U$3.3
VREG_B: C8_B.1, J2_B.2, J4_B.2, J6_B.2, J8_B.2, U$2.36, U$2.37, U$2.40, U$4.3

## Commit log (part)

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2018-08-18 Init 2019 repository
2018-08-29 Fixed LM293 Pinout in Eagle Library
2018-08-29 CAN Datalogger design rev 2
2018-09-03 Backlink to CADLAB.io has been added.
2018-09-07 CAN Datalogger board rev3 - manufacture at JLC
2018-09-12 Added DRC for Invention Studio PCB Mill
2018-09-14 Added 2018 Front ECU
2018-09-14 Began updates on Front ECU
2018-09-17 Added Right Angle MX150 connectors to library
2018-09-18 Added XT60 connector to library for Project Zero
2018-09-21 Created folder + initial .sch and .brd
2018-09-21 Added LCD to hytechdevices library
2018-09-21 increased component spacing
2018-09-21 jparkerjones: Began updates on Front ECU, Moved Software Latch to Rear ECU
2018-09-22 Labeled all componenets and organized them to make schematic later
2018-09-23 Added nets between all compnenets except LCD. Added 5 volt regulator.
2018-09-23 Small changes with schematic
2018-09-23 Finished schematic - need to verify
2018-09-23 Finished schematic (again)
2018-09-23 Verified schematic, but had to restart board
2018-09-25 Add SMD practice board rev2, update TSSOP38 breakout to fit on breadboard, silkscreen etc updates to Datalogger and Murata boards for manufacturing
2018-09-26 Added 8 and 12 Pin MX150L right angle connectors to library
2018-09-27 Added back version of file removed
2018-09-27 Finished CAN_Tester Board
2018-09-28 Added anothe rminifit and nano fit. Changed some components to through hole.
2018-09-30 Working on changes so the board can be made in the electronics lab
2018-09-30 Front ECU Layout Update
2018-10-03 Beginning work on Rear ECU
2018-10-10 Inital Changes to Rear ECU Layout Completed
    Teensy 3.5 added, Software Latch added, Right Angle Molex Connectors added
2018-10-14 Updated Layout of Front ECU
2018-10-19 Added ACS715 current sensor to the library
2018-10-24 Added Current Sensors to Rear ECU
2018-10-27 Added 4 pin and 37 pin Autosport connectors to library
2018-11-02 Began work on Rev 2 of CAN_Tester, fixing the existing issues with the Rev 1 board but not isolating the isocan yet.
2018-11-02 Added IO Expander to Library and completed basic Main ECU Schematic
2018-11-04 Updated with true isolation for separate 5V for the isocan and teensy
2018-11-04 Finished isolating and started work on fixing CAN_Tester board
2018-11-06 HV board redesign
    Removed one SSR in BMS, BSPD current sensor, jumper for fused/unfused, TSAL 60Vmin circuit, accumulator indicator, and energy meter connector. Connected output of DC/DC converter straight to TSAL out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
2018-11-10 Fixed circuit to have true isolation in CAN_Tester, and started work on new board layout
2018-11-10 Started work on routing CAN_Tester, need to adjust and run ERC/DRC.
2018-11-10 Working on board layout
2018-11-10 Finished CAN_Tester v2 board
2018-11-11 Fixed Library
2018-11-11 Adjusted traces for buttons on CAN_Tester
2018-11-12 Shortened HV board, added AND gate
    HV board shortened to 168 x 72 mm, replaced BMS SSR with AND gate.
2018-11-12 Added SOT23 package to PNP transistor
2018-11-14 Added SOT Package for NPN transistor
2018-11-18 MainECU rev2 Layout Updated
2018-11-18 Fixed spacing issues
2018-11-18 Updated Board and Schematic For Main ECU
2018-11-22 Updated Main ECU Rev2 Layout with Silkscreen and changes from design review
2018-11-28 Added silkscreen for CAN_Tester Board
2018-12-09 Updated Schematic of Main ECU to make it look better
2018-12-10 Added mechanical outline for BMS PCB
    Fillets were removed and circles imported from DXF were
    replaced with 3.6mm drills.
2018-12-12 Flipped DC/DC to the bottom, changed to HM2102NLT transformer
    Switch back to nano-fit connectors on the edge of the DC/DC converter, use cynergy relay and pulse transformer
2018-12-12 Updated cynergy relay in lib, fixed DRC issues
2018-12-14 Fixed Autosport Pinout on Main ECU
2018-12-14 Added mounting holes and make silkscreen larger on CAN Tester
2018-12-15 Init battery discharge monitoring board schematic
2018-12-16 Add ADIS16209
2018-12-16 Add rev number to board, add BMS adapter rev3
2018-12-16 Added Current Sensor L01Z150S05
2018-12-16 Moved resistor to clear space for the box
2018-12-17 Add Molex 14-pin to library, add layout for battery testing board, update silkscreen on BMS adapter board
2018-12-17 Final Updates to Main ECU Layout
2018-12-18 Fixed Wire Stubs/board outline
2018-12-18 Fixed ISOSPI spacing issues, moved silkscreen
2018-12-18 fixed mosfet heatsink issues
2018-12-18 updated thermal via locations
2018-12-19 Main ECU rev{1,2}: Ensure no autosport intersecting, ensure connectors in same location on both revisions
2018-12-19 Main ECU rev1: Swap linear regulator with switching regulator
2018-12-19 Minor silkscreen updates to HV board rev{6,7}, Update DC/DC converter package to use smaller silkscreen text size, Adjust heatsink pads in Main ECU rev2
2018-12-19 Main ECU rev2: fixed HyTech Racing logo, HV board rev{6,7}: moved silkscreen text for readability, moved traces away from mounting holes
2018-12-24 BMS segment rev8 layout, changed transformer and keystone pads
2018-12-26 init Main ECU rev1b
2018-12-26 Main ECU rev{1,2}: Update pullup/down resistor informational text, Main ECU rev1b: Update pinout to match Main ECU rev2
2018-12-27 Moved 6804 inward, fixed clearance issues
2018-12-28 Library: Add TXB0106 and TXB0104 packages, update TLP29{0,1}-4 package to correct dimensions
2018-12-28 MainECU rev3: Move RTC battery to within board footprint, update XBee package size, add SPI level shifter, Add mosfet drivers and zener diodes, Replace relay control SSRs with transistors
2018-12-28 HV rev6 & 7: Fixed capacitor value for ADC filter
2019-01-03 Main ECU: [rev2, rev3] Fix filter frequency capacitor values, [rev1b, rev3] shorten a few traces
2019-01-03 Move TXB0104 changes to rev 8 & 9
2019-01-03 Rename Main ECU rev1b -> rev3, rev3 -> rev4
2019-01-03 Main ECU rev2: Fixed capacitor values *again* (I can't math)
2019-01-03 Main ECU rev4: Fixed filter capacitor values again, added filters to current sensor outputs
2019-01-03 Rerouted for the new outline and changed pad sizes
2019-01-03 Fixed board outline width and dimension
2019-01-04 Main ECU rev3/4: Update silkscreen for manufacturing, Main ECU rev4: switch to high-side dashboard switching and flip parts on wrong side
2019-01-05 Main ECU rev4: Flip transistors to top layer, widen inverter supply trace, move some resistors for easier soldering, adjust dashboard control resistor values, clean up schematic
2019-01-05 Move Teensy label to tNames layer
2019-01-05 Main ECU rev{2,4}: Specify PNP transistor P/Ns
2019-01-09 Corrected VBAT connection for RTC coin cell
2019-01-11 Added Folder for Harness Designs and First version of Main ECU Test Harness
2019-01-12 Main ECU rev{1-4}: Add warning about RTC cell assembly, specify current sensor input capacitor value, lower XBee LED resistor to 33R; Main ECU rev{2,4}: Specify MCP3208 input capacitor value; Main EC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
2019-01-13 Updated resistor values for BJTs
2019-01-13 Added value for BJTs indicating part number
2019-01-13 Added TXB0104 level shifter and more resistor and capacitor values
2019-01-13 Added level shifter to board
2019-01-20 Main ECU rev{1-5}: Update values of LED resistors based on testing
2019-01-20 Main ECU rev{1-5}: Update values of OKI-78SR capacitors to 10uF
2019-01-20 Began replacing BJT with mosfets
2019-01-21 Placed all new MOSFETs, just need to route them and resistors
2019-01-21 Finished board layout with new MOSFETs instead of BJTs
2019-01-24 Main ECU rev5: move traces around RTC battery to reduce chance of damage during installation
2019-01-24 Main ECU rev5: Add MTK3339 GPS breakout
2019-01-25 Fixed brake circuit
2019-01-25 Main ECU rev5: Tweaked trace positions
2019-01-26 Library: Updated OKI-78SR package silkscreen to show orientation, Replaced TLV1117LV33 regulator with standardized LM3940 regulator; Main ECU rev5: Moved dashboard channel 1/2 resistors/LEDs to top l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
2019-01-27 Main ECU rev5: Add pull-up resistor to brake signal, various tweaks to traces
2019-01-27 Main ECU rev5: Replaced BMS latching SSR with mosfets
2019-01-27 Update HT03 adapter harness design
2019-01-28 Main ECU rev5: Add circuit protection components, reconfigure series SSR/LED combos
2019-01-28 BMS rev9: Processed CAM data
2019-01-28 Add gerber CAM files for priting names or values on silkscreen
2019-01-28 Main ECU rev6: init
2019-01-29 Library: Add TE DPDT relays, Modify P-mosfet symbol rotation
2019-01-29 Main ECU rev6: Implement latching without solid state relays, Fix swapped p-mosfet circuit pins, Move 5V test point to more accessible location, Change DPDT relays to TE RT424009
2019-01-29 Main ECU rev5: Specify diode P/Ns, Main ECU rev6: Update p-mosfet symbol
2019-01-30 Main ECU rev5/6: Add voltage sensing for dashboard channels 11/12 and IMD/BMS shutdown circuit outputs
2019-01-30 Main ECU rev5/6: Shorten traces, tweak silkscreen
2019-02-03 Added pull down resistors and button
2019-02-08 HV board rev10: moved LTC6820 and screw
2019-02-08 BMS segment rev9: moved resistors, modified silkscreen
2019-02-11 Init BMS layout schematic rev5
2019-02-11 Main ECU rev5/6: Move level shifter OE pin to VCCA
2019-02-13 BMS rev9, HV rev10: Small adjustments for manufacturing
2019-02-13 BMS rev9: Added termination resistor silkscreen
2019-02-14 Main ECU rev5/6: Remove unnecessary IO expander connections, add 2 smd connection pads to IO expander for testing or emergency feature expansion; Library: Lower size of smd connection pad
2019-02-20 Added resistor value for R63 in series with coil, and removed text
2019-02-27 Draft of 2019 external diagram, New connectors in EAGLE symbols library
2019-03-02 More changes to FH2019 electrical diagram
2019-03-02 Specify connector P/Ns and integrate resolver wiring in FH2019 electrical diagram
2019-03-03 BMS segment rev10 init
2019-03-03 BMS segment rev10: silkscreen adjustments
2019-03-05 Updated transistor label for cooling MOSFETs and added in Resistor/Capacitor for each snubber in schematic
2019-03-05 Added routing for snubber
2019-03-06 Flipped Resistor and capacitor posistions
2019-03-06 Added silkscreen for snubber parts
2019-03-06 Make silkscreen names larger
2019-03-07 New BMS Adapter Fuse Holder Board
2019-03-07 BMS soldering practice board
2019-03-07 BMS Test board rev1
2019-03-08 Added second 0.1 capacitor and began moving traces
2019-03-08 Small tweaks to layout around ADC
2019-03-10 Main ECU rev7: Moved ADC caps/traces again so no traces under capacitors
2019-03-11 Added bypass caps to transceiver, plus two op-amps, now need to do routing
2019-03-12 Finished routing of additional components
2019-03-14 Main ECU: Add CAN tvs diode, Add filter to 12V sense, move components and traces; Library: Add CAN tvs diode
2019-03-14 Added Charger Board to repository
2019-03-15 Main ECU: trace and silkscreen tweaks for manufacturing
2019-03-18 HV Board rev11: Amplified BMS_OK signal, added split CAN termination and TVS diode
2019-03-18 BMS Segment rev10: changed to smaller spring pads
2019-03-19 added jumper and added capacitor to 5v reg
2019-03-19 Charger Control Board with suggested modifications
2019-03-21 HV Board: Added bypass caps to LTC6820 and SPI level shifter, rerouted under Teensy, rerouted GND/Power to 5V regulator, Silkscreen updates for mfg
2019-03-25 Charger control board with modifications to control external relay board
2019-03-27 Made final changes to Charger Boards. Added a relay to Library
2019-03-30 Tweaked BMS test board, added rev2 with swapped SPI mode resistors
2019-03-30 Modified charger board silkscreens for manufacturing
2019-03-31 Update external diagram to remove ground loops
2019-04-01 Final version of HV board rev11 sent for mfg
2019-04-02 Initial vehicle wiring diagram with Main ECU forward of firewall
2019-04-18 New wiring harness diagram with Main ECU in front of firewall
2019-05-15 Manufactured versions of Main ECU rev7 and rev8
2019-05-15 External Diagram rev2 used at Formula Hybrid
2019-05-15 Add March panelized orders
2019-07-22 Started quick fix rev2
2019-08-01 Added 555timer solder test board
2019-08-23 Adjusted schematic for v2 of charger control board
2019-08-23 Finished charger control board rev 2
2019-08-23 Minor changes that didn't get saved for some reason
2019-08-25 Made folder names more consistent and organized files off mmain directory
2019-09-15 Added gerber zips
2019-09-15 Schematic/Board images
